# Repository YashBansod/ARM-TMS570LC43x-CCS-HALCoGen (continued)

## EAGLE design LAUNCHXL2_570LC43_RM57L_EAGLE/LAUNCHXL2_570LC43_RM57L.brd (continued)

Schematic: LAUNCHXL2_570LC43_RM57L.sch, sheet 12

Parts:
C58, C59, C60, C61, C63, C68: 0.1uF; C0201; PARTNO CL03A104MQ3NNNC
C62, C70: 0.01uF; C0201; PARTNO CL03A103KQ3NNNC
C65, C67, C71: 1uF; C0402K; PARTNO GRM155R60J105KE19D
J11: MAGJACKARJCO2-111006E; DUAL_ABRACRON_ARJC02_111006K_PULSE_J00-0065NL; PARTNO ARJC02-111006K
R8, R9, R11, R47: 0; R0201; PARTNO RC0201JR-070RL
R20: 4.87K; R0201; PARTNO CRCW02014K87FKED
R23, R24, R36, R37, R38, R46: 49.9; R0201; PARTNO CRCW020149R9FNED
RP11: 2.2K; RP8_1506_1606; PARTNO MNR18E0APJ222
U4: DP83630_RHS_48; SQA48A; PARTNO DP83630SQE/NOPB

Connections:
+3V3: J11.9 (AN1), J11.12 (AN2), R8.1, R9.1, R11.1, RP11.7 (1), RP11.11 (1), RP11.13 (1); also elsewhere on the board
ECLK1T: U4.34 (XIN); also elsewhere on the board
ESHLD: J11.7 (SH1), J11.8 (SH2), R47.1
ETHRD_N: J11.6 (RD-), R37.2, U4.13 (RD-)
ETHRD_P: J11.3 (RD+), R36.2, U4.14 (RD+)
ETHTD_N: J11.2 (TD-), R24.2, U4.16 (TD-)
ETHTD_P: J11.1 (TD+), R23.2, U4.17 (TD+)
GIOA_3/N2HET2_2: RP11.4 (2), U4.7 (PWRDOWN/INTN); also elsewhere on the board
GIOA_4: U4.29 (RESET_N); also elsewhere on the board
GND: C58.2, C59.2, C60.2, C61.2, C62.2, C63.2, C65.2, C67.2, C68.2, C70.2, C71.2, R20.1, R47.2, RP11.1, RP11.3 (1), RP11.9 (1), U4.15 (CD_VSS), U4.18 (ANAVSS), U4.35 (IO_CORE_VSS), U4.47 (IO_VSS), U4.49 (DAP); also elsewhere on the board
MDCLK: U4.31 (MDC); also elsewhere on the board
MDIO: RP11.8 (2), U4.30 (MDIO); also elsewhere on the board
MII_COL: U4.42 (COL); also elsewhere on the board
MII_CRS: RP11.12 (2), U4.40 (CRS/CRS_DV); also elsewhere on the board
MII_RXCLK/MII_RX_AVCLK4: U4.38 (RX_CLK); also elsewhere on the board
MII_RXD_0: U4.46 (RXD_0); also elsewhere on the board
MII_RXD_1: U4.45 (RXD_1); also elsewhere on the board
MII_RXD_2: U4.44 (RXD_2); also elsewhere on the board
MII_RXD_3: U4.43 (RXD_3); also elsewhere on the board
MII_RX_DV: RP11.10 (2), U4.39 (RX_DV); also elsewhere on the board
MII_RX_ER: RP11.14 (2), U4.41 (RX_ER); also elsewhere on the board
MII_TXCLK/MII_TX_AVCLK4: U4.1 (TX_CLK); also elsewhere on the board
MII_TXD_0: U4.3 (TXD_0); also elsewhere on the board
MII_TXD_1: U4.4 (TXD_1); also elsewhere on the board
MII_TXD_2: U4.5 (TXD_2); also elsewhere on the board
MII_TXD_3: U4.6 (TXD_3); also elsewhere on the board
MII_TXEN: U4.2 (TX_EN); also elsewhere on the board
N2HET1_15/MIBSPI1NCS_4/N2HET2_22/ECAP1: U4.27 (LED_SPEED/FX_SD); also elsewhere on the board
N2HET1_21/EMIF_NDQM_2: U4.36 (GPIO8); also elsewhere on the board
N2HET1_25: U4.37 (GPIO9); also elsewhere on the board
N2HET1_31: U4.25 (GPIO4); also elsewhere on the board
N2HET2_4: R38.2, U4.28 (LED_LINK); also elsewhere on the board
N2HET2_5: R46.2, U4.26 (LED_ACT); also elsewhere on the board
N2HET2_6: U4.21 (GPIO1); also elsewhere on the board
N2HET2_22: U4.22 (GPIO2); also elsewhere on the board
N2HET2_23: U4.23 (GPIO3); also elsewhere on the board
unnamed: J11.10 (CAT1), R38.1
unnamed: J11.11 (CAT2), R46.1
PHYAVDD: C63.1, C70.1, C71.1, R9.2, U4.19 (ANA33VDD)
PHYIOVDD: C62.1, C67.1, C68.1, R8.2, U4.32 (IO_VDD), U4.48 (IO_VDD_2)
PHY_VCT: C58.1, C59.1, C60.1, C61.1, C65.1, J11.4 (CT1), J11.5 (CT2), R11.2, R23.1, R24.1, R36.1, R37.1
RBIAS: R20.2, U4.20 (VREF)

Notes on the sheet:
PHY ADDRESS ================ PHYADDR[4:0] = 00001b MCU & PHY Pulls Match PHYAD0 (COL) - PU PHYAD1 (RXD0) - PD PHYAD2 (RXD1) - PD PHYAD3 (RXD2) - PD PHYAD4 (RXD3) - PD
FOR CENTER TAPS
spare

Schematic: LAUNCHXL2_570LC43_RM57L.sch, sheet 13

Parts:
J12, J13: DF40C-60DP-0.4V(51); PARTNO DF40C-60DP-0.4V(51)

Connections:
+3V3: J12.3, J12.4, J12.59, J12.60, J13.3, J13.4, J13.59, J13.60; also elsewhere on the board
EMIF_ADDR_0/N2HET2_1: J13.50; also elsewhere on the board
EMIF_ADDR_1/N2HET2_3: J13.48; also elsewhere on the board
EMIF_ADDR_6/RTP_DATA_13/N2HET2_11: J13.44; also elsewhere on the board
EMIF_ADDR_7/RTP_DATA_12/N2HET2_13: J13.42; also elsewhere on the board
EMIF_ADDR_8/RTP_DATA_11/N2HET2_15: J13.38; also elsewhere on the board
EMIF_ADDR_9/RTP_DATA_10: J13.36; also elsewhere on the board
EMIF_ADDR_10/RTP_DATA_9: J13.32; also elsewhere on the board
EMIF_ADDR_11/RTP_DATA_8: J13.39; also elsewhere on the board
EMIF_ADDR_12/RTP_DATA_6: J13.33; also elsewhere on the board
EMIF_ADDR_13/RTP_DATA_5: J13.29; also elsewhere on the board
EMIF_ADDR_14/RTP_DATA_4: J13.27; also elsewhere on the board
EMIF_ADDR_15/RTP_DATA_3: J13.23; also elsewhere on the board
EMIF_ADDR_16/RTP_DATA_2: J13.21; also elsewhere on the board
EMIF_ADDR_17/RTP_DATA_1: J13.17; also elsewhere on the board
EMIF_ADDR_18/RTP_DATA_0: J13.15; also elsewhere on the board
EMIF_ADDR_19/RTP_NENA: J13.11; also elsewhere on the board
EMIF_ADDR_20/RTP_NSYNC: J13.9; also elsewhere on the board
EMIF_ADDR_21/RTP_CLK: J13.5; also elsewhere on the board
EMIF_BA_1/N2HET2_5: J13.35; also elsewhere on the board
EMIF_NCS_0/RTP_DATA_15/N2HET2_7: J12.5; also elsewhere on the board
EMIF_NCS_2/GIOB_4: J12.9; also elsewhere on the board
EMIF_NCS_3/RTP_DATA_14/N2HET2_9: J12.11; also elsewhere on the board
EMIF_NCS_4/RTP_DATA_7/GIOB_5: J12.15; also elsewhere on the board
EMIF_NWE/EMIF_RNW: J12.51; also elsewhere on the board
ETMDATA_2: J12.29; also elsewhere on the board
ETMDATA_3: J12.33; also elsewhere on the board
ETMDATA_4: J12.35; also elsewhere on the board
ETMDATA_5: J12.39; also elsewhere on the board
ETMDATA_6: J12.41; also elsewhere on the board
ETMDATA_7: J12.45; also elsewhere on the board
ETMDATA_8/EMIF_ADDR_5: J12.47; also elsewhere on the board
ETMDATA_9/EMIF_ADDR_4: J13.6; also elsewhere on the board
ETMDATA_10/EMIF_ADDR_3: J13.8; also elsewhere on the board
ETMDATA_11/EMIF_ADDR_2: J13.12; also elsewhere on the board
ETMDATA_12/EMIF_BA_0: J13.41; also elsewhere on the board
ETMDATA_13/EMIF_NOE: J13.45; also elsewhere on the board
ETMDATA_14/EMIF_NDQM_1: J13.47; also elsewhere on the board
ETMDATA_15/EMIF_NDQM_0: J13.51; also elsewhere on the board
ETMDATA_16/EMIF_DATA_0: J12.27; also elsewhere on the board
ETMDATA_17/EMIF_DATA_1: J12.23; also elsewhere on the board
ETMDATA_18/EMIF_DATA_2: J12.21; also elsewhere on the board
ETMDATA_19/EMIF_DATA_3: J12.17; also elsewhere on the board
ETMDATA_20/EMIF_DATA_4: J13.14; also elsewhere on the board
ETMDATA_21/EMIF_DATA_5: J13.18; also elsewhere on the board
ETMDATA_22/EMIF_DATA_6: J13.20; also elsewhere on the board
ETMDATA_23/EMIF_DATA_7: J13.24; also elsewhere on the board
ETMDATA_24/EMIF_DATA_8/N2HET2_24/MIBSPI5NCS_4: J13.26; also elsewhere on the board
ETMDATA_25/EMIF_DATA_9/N2HET2_25/MIBSPI5NCS_5: J13.30; also elsewhere on the board
EXTERNAL_DEBUG: J12.20; also elsewhere on the board
FDONE: J13.54; also elsewhere on the board
FPROG: J12.42; also elsewhere on the board
FSCLK: J13.55; also elsewhere on the board
FSIMO: J13.53; also elsewhere on the board
FSOMI: J13.56; also elsewhere on the board
FTCK: J12.30; also elsewhere on the board
FTDI: J12.36; also elsewhere on the board
FTDO: J12.32; also elsewhere on the board
FTMS: J12.38; also elsewhere on the board
GND: J12.1, J12.2, J12.7, J12.10, J12.13, J12.16, J12.19, J12.22, J12.25, J12.28, J12.31, J12.34, J12.37, J12.40, J12.43, J12.46, J12.49, J12.52, J12.57, J12.58, J13.1, J13.2, J13.7, J13.10, J13.13, J13.16, J13.19, J13.22, J13.25, J13.28, J13.31, J13.34, J13.37, J13.40, J13.43, J13.46, J13.49, J13.52, J13.57, J13.58; also elsewhere on the board
HERCULES_MR_PB: J12.18; also elsewhere on the board
HERCULES_NRST: J12.55; also elsewhere on the board
HERCULES_NTRST: J12.26; also elsewhere on the board
HERCULES_RTCK: J12.24; also elsewhere on the board
HERCULES_TCK: J12.6; also elsewhere on the board
HERCULES_TDI: J12.14; also elsewhere on the board
HERCULES_TDO: J12.12; also elsewhere on the board
HERCULES_TMS: J12.8; also elsewhere on the board
MIBSPI1CLK: J12.44; also elsewhere on the board
N2HET1_8/MIBSPI1SIMO_1/MII_TXD_3: J12.48; also elsewhere on the board
N2HET1_10/MIBSPI4NCS_4/MII_TXCLK/MII_TX_AVCLK4/NTZ1_3: J12.50; also elsewhere on the board
N2HET1_17/EMIF_NOE/SCI4RX: J12.54; also elsewhere on the board
N2HET1_19/EMIF_NDQM_0/SCI4TX: J12.56; also elsewhere on the board
NERROR: J12.53; also elsewhere on the board

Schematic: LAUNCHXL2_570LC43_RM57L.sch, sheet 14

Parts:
J14, J15: DF40C-60DP-0.4V(51); PARTNO DF40C-60DP-0.4V(51)

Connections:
+3V3: J14.3, J14.4, J14.59, J14.60, J15.3, J15.4, J15.59, J15.60; also elsewhere on the board
AD1EVT/MII_RX_ER/RMII_RX_ER/NTZ1_1: J14.12; also elsewhere on the board
AD2IN_16: J14.47; also elsewhere on the board
AD2IN_17: J14.51; also elsewhere on the board
AD2IN_18: J14.53; also elsewhere on the board
AD2IN_19: J14.55; also elsewhere on the board
AD2IN_20: J14.56; also elsewhere on the board
AD2IN_21: J14.54; also elsewhere on the board
AD2IN_22: J14.50; also elsewhere on the board
AD2IN_23: J14.48; also elsewhere on the board
DMM_CLK: J14.5; also elsewhere on the board
DMM_DATA_0: J14.15; also elsewhere on the board
DMM_DATA_1: J14.16; also elsewhere on the board
DMM_NENA: J14.9; also elsewhere on the board
DMM_SYNC: J14.11; also elsewhere on the board
EMIF_CKE: J15.48; also elsewhere on the board
EMIF_CLK/ECLK2: J15.50; also elsewhere on the board
EMIF_NCAS/GIOB_3: J15.38; also elsewhere on the board
EMIF_NRAS/GIOB_6: J15.42; also elsewhere on the board
EMIF_NWAIT/GIOB_7: J15.44; also elsewhere on the board
EPWM1A: J15.9; also elsewhere on the board
EPWM1B: J15.5; also elsewhere on the board
ETMDATA_0: J15.6; also elsewhere on the board
ETMDATA_1: J15.8; also elsewhere on the board
ETMDATA_26/EMIF_DATA_10/N2HET2_26: J15.36; also elsewhere on the board
ETMDATA_27/EMIF_DATA_11/N2HET2_27: J15.32; also elsewhere on the board
ETMDATA_28/EMIF_DATA_12/N2HET2_28/GIOA_0: J15.30; also elsewhere on the board
ETMDATA_29/EMIF_DATA_13/N2HET2_29/GIOA_1: J15.26; also elsewhere on the board
ETMDATA_30/EMIF_DATA_14/N2HET2_30/GIOA_3: J15.24; also elsewhere on the board
ETMDATA_31/EMIF_DATA_15/N2HET2_31/GIOA_4: J15.20; also elsewhere on the board
ETMTRACECLKIN/EXTCLKIN2/GIOA_5: J15.18; also elsewhere on the board
ETMTRACECLKOUT/GIOA_6: J15.12; also elsewhere on the board
ETMTRACECTL/GIOA_7: J15.14; also elsewhere on the board
FINT: J15.54; also elsewhere on the board
FM0: J14.42; also elsewhere on the board
FM1: J14.44; also elsewhere on the board
FM2: J14.45; also elsewhere on the board
GIOB_2/DCAN4TX: J14.8; also elsewhere on the board
GIOB_3/DCAN4RX: J14.6; also elsewhere on the board
GND: J14.1, J14.2, J14.7, J14.10, J14.13, J14.19, J14.22, J14.25, J14.28, J14.31, J14.34, J14.37, J14.40, J14.43, J14.46, J14.49, J14.52, J14.57, J14.58, J15.1, J15.2, J15.7, J15.10, J15.13, J15.16, J15.19, J15.22, J15.25, J15.28, J15.31, J15.34, J15.37, J15.40, J15.43, J15.46, J15.49, J15.52, J15.57, J15.58; also elsewhere on the board
MIBSPI1CLK: J15.56; also elsewhere on the board
MIBSPI1NCS_0/MIBSPI1SOMI_1/MII_TXD_2/ECAP6: J15.39; also elsewhere on the board
MIBSPI1NCS_1/MII_COL/N2HET1_17/EQEP1S: J15.41; also elsewhere on the board
MIBSPI1NCS_2/MDIO/N2HET1_19: J15.45; also elsewhere on the board
MIBSPI1NENA/MII_RXD_2/N2HET1_23/ECAP4: J15.51; also elsewhere on the board
MIBSPI1SIMO_0: J15.53; also elsewhere on the board
MIBSPI1SOMI_0: J15.55; also elsewhere on the board
MIBSPI3NCS_0/AD2EVT/EQEP1I: J14.14; also elsewhere on the board
MIBSPI3NCS_1/MDCLK/N2HET1_25: J15.15; also elsewhere on the board
MIBSPI3NCS_2/I2C1_SDA/N2HET1_27/NTZ1_2: J15.17; also elsewhere on the board
MIBSPI3NCS_3/I2C1_SCL/N2HET1_29/NTZ1_1: J15.21; also elsewhere on the board
MIBSPI5CLK/DMM_DATA_4/MII_TXEN/RMII_TXEN: J14.21; also elsewhere on the board
MIBSPI5NCS_0/DMM_DATA_5/EPWM4A: J14.20; also elsewhere on the board
MIBSPI5NCS_1/DMM_DATA_6: J14.23; also elsewhere on the board
MIBSPI5NCS_2/DMM_DATA_2: J14.17; also elsewhere on the board
MIBSPI5NCS_3/DMM_DATA_3: J14.18; also elsewhere on the board
MIBSPI5NENA/DMM_DATA_7/MII_RXD_3/ECAP5: J14.24; also elsewhere on the board
MIBSPI5SIMO_0/DMM_DATA_8/MII_TXD_1/RMII_TXD_1: J14.27; also elsewhere on the board
MIBSPI5SIMO_1/DMM_DATA_9/AD1EXT_SEL_0: J14.26; also elsewhere on the board
MIBSPI5SIMO_2/DMM_DATA_10/AD1EXT_SEL_1: J14.29; also elsewhere on the board
MIBSPI5SIMO_3/DMM_DATA_11/I2C2_SDA/AD1EXT_SEL_2: J14.30; also elsewhere on the board
MIBSPI5SOMI_0/DMM_DATA_12/MII_TXD_0/RMII_TXD_0: J14.33; also elsewhere on the board
MIBSPI5SOMI_1/DMM_DATA_13/AD1EXT_SEL_3: J14.32; also elsewhere on the board
MIBSPI5SOMI_2/DMM_DATA_14/AD1EXT_SEL_4: J14.35; also elsewhere on the board
MIBSPI5SOMI_3/DMM_DATA_15/I2C2_SCL/AD1EXT_ENA: J14.36; also elsewhere on the board
N2HET1_1/MIBSPI4NENA/N2HET2_8/EQEP2A: J15.33; also elsewhere on the board
N2HET1_3/MIBSPI4NCS_0/N2HET2_10/EQEP2B: J15.35; also elsewhere on the board
N2HET1_12/MIBSPI4NCS_5/MII_CRS/RMII_CRS_DV: J15.23; also elsewhere on the board
N2HET1_20/EMIF_NDQM_1/EPWM6B: J15.11; also elsewhere on the board
N2HET1_24/MIBSPI1NCS_5/MII_RXD_0/RMII_RXD_0: J15.47; also elsewhere on the board
N2HET1_26/MII_RXD_1/RMII_RXD_1: J15.29; also elsewhere on the board
N2HET1_28/MII_RXCLK/RMII_REFCLK/MII_RX_AVCLK4: J14.38; also elsewhere on the board
N2HET1_30/MII_RX_DV/EQEP2S: J15.27; also elsewhere on the board
N2HET2_19/LIN2RX: J14.39; also elsewhere on the board
N2HET2_20/LIN2TX: J14.41; also elsewhere on the board

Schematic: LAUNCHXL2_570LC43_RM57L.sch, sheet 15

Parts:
LED7, LED8: GRN; CHIPLED_0603; PARTNO QBLP601-AG
R7: 49.9; R0201; PARTNO CRCW020149R9FNED
R30, R31: 330K; R0201; PARTNO RC0603F334CS
R34, R35: 220K; R0201; PARTNO RC0603F224CS
RP12: 2.2K; RP8_1506_1606; PARTNO MNR18E0APJ222
U7: TM4C129ENCPDT; PDT128; PARTNO TM4C129ENCPDTI3

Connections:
+1V2: U7.127 (PD6\AIN5\SSI2XDAT3\T4CCP0\U2RTS\USB0EPEN); also elsewhere on the board
+3V3: R35.2; also elsewhere on the board
+5V_USB: R34.2, U7.96 (PB1\CAN1TX\I2C5SDA\T4CCP1\U1TX\USB0VBUS); also elsewhere on the board
EXTERNAL_DEBUG: U7.41 (PA7\EPI0S9\I2C6SDA\SSI0XDAT3\T3CCP1\U2T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); also elsewhere on the board
FDONE: U7.71 (PM7\T5CCP1\TMPR0\U0RI); also elsewhere on the board
FINT: U7.6 (PQ1\EPI0S21\SSI3FSS); also elsewhere on the board
FM0: U7.74 (PM4\T4CCP0\TMPR3\U0CTS); also elsewhere on the board
FM1: U7.73 (PM5\T4CCP1\TMPR2\U0DCD); also elsewhere on the board
FM2: U7.72 (PM6\T5CCP0\TMPR1\U0DSR); also elsewhere on the board
FPROG: U7.102 (PQ4\DIVSCLK\U1RX); also elsewhere on the board
FSCLK: U7.5 (PQ0\EPI0S20\SSI3CLK); also elsewhere on the board
FSIMO: U7.11 (PQ2\EPI0S22\SSI3XDAT0); also elsewhere on the board
FSOMI: U7.27 (PQ3\EPI0S23\SSI3XDAT1); also elsewhere on the board
FTCK: U7.112 (PN5\EPI0S35\I2C2SCL\U1RI\U3CTS); also elsewhere on the board
FTDI: U7.110 (PN3\EPI0S30\U1DSR\U2CTS); also elsewhere on the board
FTDO: U7.111 (PN4\EPI0S34\I2C2SDA\U1DTR\U3RTS); also elsewhere on the board
FTMS: U7.109 (PN2\EPI0S29\U1DCD\U2RTS); also elsewhere on the board
GND: LED7.C, LED8.C, R30.1, R31.1, U7.61 (PK6\EN0LED1\EPI0S25\I2C4SCL\M0FAULT1), U7.62 (PK5\EN0LED2\EPI0S31\I2C3SDA\M0PWM7); also elsewhere on the board
HERCULES_ICORE: U7.15 (PE0\AIN3\U1RTS); also elsewhere on the board
HERCULES_MR_PB: U7.40 (PA6\EPI0S8\I2C6SCL\SSI0XDAT2\T3CCP0\U2R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); also elsewhere on the board
HERCULES_NRST: U7.25 (PC4\C1-\EPI0S7\U7RX); also elsewhere on the board
HERCULES_NTRST: U7.107 (PN0\U1RTS); also elsewhere on the board
HERCULES_RTCK: U7.108 (PN1\U1CTS); also elsewhere on the board
HERCULES_TCK: R7.2; also elsewhere on the board
HERCULES_TDI: U7.38 (PA5\I2C7SDA\SSI0XDAT1\T2CCP1\U3TX); also elsewhere on the board
HERCULES_TDO: U7.37 (PA4\I2C7SCL\SSI0XDAT0\T2CCP0\U3RX); also elsewhere on the board
HERCULES_TMS: U7.36 (PA3\I2C8SDA\SSI0FSS\T1CCP1\U4TX); also elsewhere on the board
ITCK: U7.100 (PC0\SWCLK\TCK); also elsewhere on the board
ITDI: U7.98 (PC2\TDI); also elsewhere on the board
ITDO: U7.97 (PC3\SWO\TDO); also elsewhere on the board
ITMS: U7.99 (PC1\SWDIO\TMS); also elsewhere on the board
LIN1RX: U7.34 (PA1\CAN0TX\I2C9SDA\T0CCP1\U0TX); also elsewhere on the board
LIN1TX: U7.33 (PA0\CAN0RX\I2C9SCL\T0CCP0\U0RX); also elsewhere on the board
unnamed: RP12.3 (1), U7.4 (PD3\AIN12\I2C8SDA\SSI2CLK\T1CCP1)
unnamed: LED7.A, RP12.4 (2)
unnamed: RP12.1, U7.3 (PD2\AIN13\C2O\I2C8SCL\SSI2FSS\T1CCP0)
unnamed: R7.1, U7.35 (PA2\I2C8SCL\SSI0CLK\T1CCP0\U4RX)
unnamed: R31.2, R35.1, U7.126 (PD5\AIN6\SSI1XDAT3\T3CCP1\U2TX)
unnamed: R30.2, R34.1, U7.1 (PD0\AIN15\C0O\I2C7SCL\SSI2XDAT1\T0CCP0)
unnamed: LED8.A, RP12.2
USBD_N: U7.93 (PL7\T1CCP1\USB0DM); also elsewhere on the board
USBD_P: U7.94 (PL6\T1CCP0\USB0DP); also elsewhere on the board
USB_HIPWR_ENA: U7.118 (PP0\C2+\SSI3XDAT2\U6RX); also elsewhere on the board
USB_ID: U7.95 (PB0\CAN1RX\I2C5SCL\T4CCP0\U1RX\USB0ID); also elsewhere on the board
VERSION_0: U7.63 (PK4\EN0LED0\EPI0S32\I2C3SCL\M0PWM6)
VERSION_3: U7.60 (PK7\EPI0S24\I2C4SDA\M0FAULT2\RTCCLK\U0RI)

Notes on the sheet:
VERSION_1
VERSION_2
VERSION = 1001b
XDS110 DEBUG PROBE

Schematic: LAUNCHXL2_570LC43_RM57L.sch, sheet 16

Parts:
C34, C39: 33pF; C0201; PARTNO CC0201JRNPO8BN330
C35, C40, C42, C49: 0.01uF; C0201; PARTNO CL03A103KQ3NNNC
C36, C37, C41, C44: 1000pF; C0201; PARTNO CC0201KRX7R8BB102
C38, C43, C45, C47, C48: 0.1uF; C0201; PARTNO CL03A104MQ3NNNC
C46, C50: 10uF; C0805K; PARTNO C0805C106K8PACTU
J19: FTSH-105-01-F-DV_SMD; FTSH-105-01-F-DV; PARTNO PJ-002BH-SMT-TR
R5: 4.87K; R0201; PARTNO CRCW02014K87FKED
R40: 49.9; R0201; PARTNO CRCW020149R9FNED
RP12: 2.2K; RP8_1506_1606; PARTNO MNR18E0APJ222
U7: TM4C129ENCPDT; PDT128; PARTNO TM4C129ENCPDTI3
U8: LM4040D30_DBZ_3; DBZ3; PARTNO LM4040D20IDBZR
Y2: 16.00MHZ; CSM-3X; PARTNO ECS-160-20-3X-TR

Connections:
+1V2_TM4C: C47.1, C49.1, C50.1, U7.87 (VDDC), U7.115 (VDDC)
+3V3: C35.1, C36.1, C37.1, C38.1, C40.1, C41.1, C42.1, C43.1, C44.1, C45.1, C46.1, J19.1, R40.1, RP12.5 (1), U7.7 (VDD), U7.8 (VDDA), U7.16 (VDD), U7.26 (VDD), U7.28 (VDD), U7.39 (VDD), U7.47 (VDD), U7.51 (VDD), U7.52 (VDD), U7.68 (VBAT), U7.69 (VDD), U7.79 (VDD), U7.90 (VDD), U7.101 (VDD), U7.113 (VDD), U7.122 (VDD); also elsewhere on the board
GND: C34.2, C35.2, C36.2, C37.2, C38.2, C39.2, C40.2, C41.2, C42.2, C43.2, C44.2, C45.2, C46.2, C47.2, C48.2, C49.2, C50.2, J19.3, J19.5, J19.7, J19.9, R5.1, U7.10 (GNDA), U7.17 (GND), U7.48 (GND), U7.55 (GND), U7.58 (GND), U7.64 (!WAKE), U7.66 (XOSC0), U7.80 (GND), U7.114 (GND), U8.2 (ANODE); also elsewhere on the board
IRSTN: J19.10, RP12.6 (2), U7.70 (!RST)
ITCK: J19.4; also elsewhere on the board
ITDI: J19.8; also elsewhere on the board
ITDO: J19.6; also elsewhere on the board
ITMS: J19.2; also elsewhere on the board
unnamed: R5.2, U7.59 (RBIAS)
OSC0: C34.1, U7.88 (OSC0), Y2.2
OSC1: C39.1, U7.89 (OSC1), Y2.1
VREFA+: C48.1, R40.2, U7.9 (VREFA+), U8.1 (CATHODE)

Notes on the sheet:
3.0V ADC REFERENCE
J19 not intended for normal use. Locate on Back Side / Cover in SM.
XDS110 DEBUG PROBE

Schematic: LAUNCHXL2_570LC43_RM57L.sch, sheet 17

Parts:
C51: 4.7uF; C0603K; PARTNO CC0603KRX5R5BB475
C52: 0.1uF; C0201; PARTNO CL03A104MQ3NNNC
C53, C54: 4700pF; C0201; PARTNO GRM033R71A472KA01D
C55: 100uF; C1206K; PARTNO GRM31CR60J107ME39L
FB1, FB2: 30 OHM @ 100MHz; R0603; PARTNO CIS10P300AC
FID1, FID2, FID3, FID4, FID5: DNP; FIDUCIAL_1MM; PARTNO BOM_EXCLUDE
J16: USB_MICRO_B_SMD; PARTNO 10118192-0001LF
J17: JACK-PLUGCUI_PJ002BH; CUI_PJ002BH; PARTNO FTSH-105-01-F-DV
JP6: SHORT; JP1_SHORT; PARTNO GEC02DABN-M30
LED9: RED; CHIPLED_0603; PARTNO LS Q976-NR-1
MH1, MH2, MH3, MH4: DNP; MH_94_200; PARTNO BOM_EXCLUDE
PAD9, PAD10, PAD11, PAD12: DNP; 2,54/1,1; PARTNO BOM_EXCLUDE
PTC1: 3A IH / 5A IT; R1812; PARTNO 0ZCG0300FF2B
R43: 220K; R0201; PARTNO RC0603F224CS
R44: 1M; R0201; PARTNO RC0201JR-071ML
R45: 61.9K; R0201; PARTNO CRCW020161K9FKED
RP12: 2.2K; RP8_1506_1606; PARTNO MNR18E0APJ222
U3: TPD4E004_DRY_6; DRY6; PARTNO TPD4E004DRYR
U9: TPS2553_DBV_6; DBV6; PARTNO TPS2553DBVR

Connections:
5V_USB_LIMITED: JP6.1, U9.6 (OUT)
+5V: C55.1, JP6.2, PTC1.1; also elsewhere on the board
+5V_JACK: J17.1A (3), J17.1B (3), PTC1.2
+5V_USB: C51.1, FB1.2 (B), RP12.11 (1), RP12.14 (2), U3.5 (IO4), U9.1 (IN); also elsewhere on the board
GND: C51.2, C52.2, C54.2, C55.2, FB2.2 (B), J17.2 (1), J17.3 (2), PAD9.1, PAD10.1, PAD11.1, PAD12.1, R43.2, U9.2 (GND); also elsewhere on the board
ILIM: C54.1, R43.1, R45.2, U9.5 (ILIM)
unnamed: LED9.A, RP12.12 (2)
unnamed: C52.1, RP12.13 (1), U9.3 (EN)
USBD_N: J16.2 (D-), U3.1 (IO1); also elsewhere on the board
USBD_P: J16.3 (D+), U3.2 (IO2); also elsewhere on the board
USBVDD: FB1.1 (A), J16.1 (USBVDD), U3.6 (VCC)
USBVSS: C53.1, FB2.1 (A), J16.5 (USBVSS), R44.2, U3.3 (GND)
USB_HIPWR_ENA: R45.1; also elsewhere on the board
USB_ID: J16.4 (ID), U3.4 (IO3); also elsewhere on the board
USB_PWRFAULT: LED9.C, U9.4 (*FAULT)
USB_SHIELD: C53.2, J16.S1, J16.S2, J16.S3, J16.S4, J16.S5, J16.S6, R44.1

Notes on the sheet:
CURRENT LIMITING FOR BUS POWERED OPERATION
DEBUG USB XDS110
REMOVE JUMPER TO POWER THROUGH BARREL JACK
FIDUCIALS
GND POINTS
BOARD
QFP
MNT HOLES

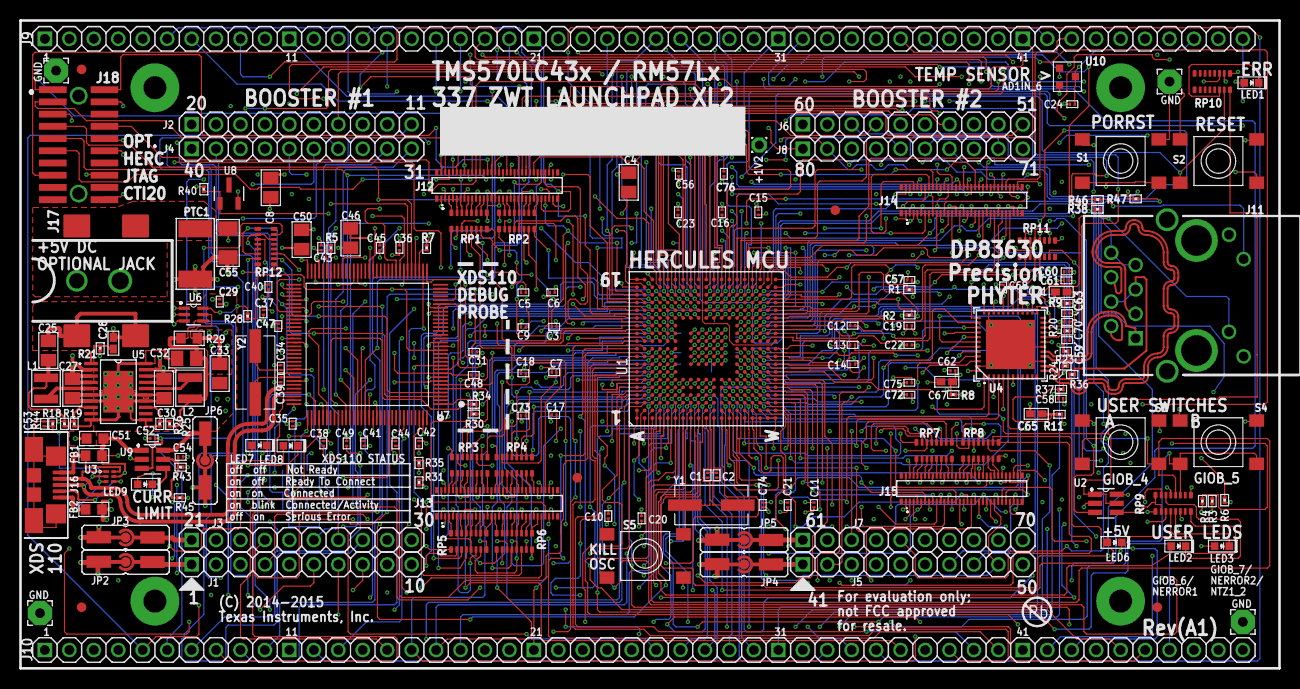
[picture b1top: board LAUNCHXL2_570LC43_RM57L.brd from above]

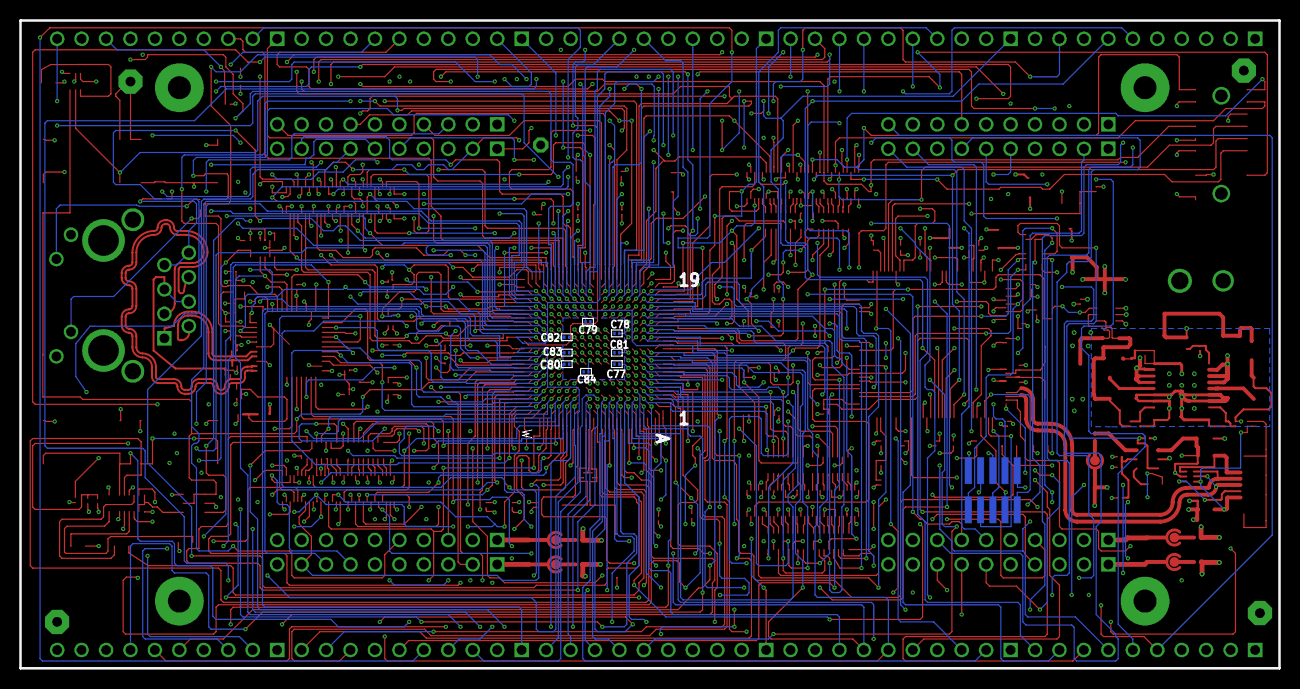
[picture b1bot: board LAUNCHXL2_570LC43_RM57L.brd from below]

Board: 6 copper layers, 130.8 x 67.3 mm, 193 parts (9 on the bottom side), 407 nets.

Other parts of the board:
DRILEGEND: DRILEGEND

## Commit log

2016-12-11 This CCS Project demonstates the toggling of user LEDs on Hercules TMS570LC43x Development board. The GIOB 6 & 7 are toggled with a 1 second delay created by wasting machine cycles.
    This code can be edited to operate on any GIO on the board.
2016-12-11 The following project demonstrates the toggling of user LEDs on the Hercules TMS570LC43x Development board using CCS. The LEDs are toggled with a delay of 1000 milli-second using the RTI (Real Time I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
    The following code can be edited to generate a code for
    timer interrupt operations.
2016-12-11 Added Comments to explain the code.
2016-12-11 Corrected a comment in the code.
2016-12-11 The following code toggles the hetPORT1 pin 1 & 2 with a duration of 1 second by wasting machine cycles. The code is written on CCS 6 and Driver Libraries were created using the TI's HALCoGen.
    This code can be edited to operate on the hetPORT 1 & 2.
2016-12-11 The following code demonstrates the toggling of hetPORT1 pin 1 & 2 with a duration of 100 milli-seconds using the RTI (Real Time Interrupts). The code is written using CCS and HALCoGen.
    This code can be edited to operate the hetPORT 1 & 2 with real time
    interrupts.
2016-12-13 This code sends an array of predefined ASCII Characters to the SCI configured as UART port to an UART enabled device. The Code is written using CCS and HALCoGen.
    This code can be used to publish data through UART contineously from
    the microcontroller.
2016-12-13 This program recieves ASCII characters from a UART enabled device and stores it in a variable. The variable is also echoed back to the user. Also initially a prompt is transmitted to the user for ent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
    This can be modified to recieve data from sensors sending value through
    UART, or control microcontroller through UART
2016-12-15 This project glows the userLEDs when the userBUTTONs are pressed. The project was made using CCS and HALCoGen.
    The code can be edited to have any digital output controlled by a digital
    input.
2016-12-15 Variable names changed. Minor modifications done.
2016-12-15 Variable names changed. Minor modifications made.
2016-12-15 Minor code changes. (rearranged)
2016-12-15 The following project configures the hetPORT1 to generate a PWM of 4.25% duty cycle on PWM0, HET1_8 pin. The code is made using CCS and HALCoGen.
    The following code can be made to give a fixed PWM signal
    to hetPORT 1 and 2 pins.
2016-12-15 The following project generates a varying PWM on HET1_8 pin. The Period is 20ms and inital duty cycle 4.00%(800us). The duty cycle can be changed in steps of 0.01 by pressing the userSWITCH A & B. Th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
    The code can be edited to obtain varying duty cycles on
    HET PORT 1 & 2.
2017-01-21 The project sends the ADC1[6] value through the UART1. The project was made using CCS and HALCoGen. The code can be edited to transmit any ADC reading or Digital reading through a UART connection.
2017-01-21 Transmit data of multiple ADC channels through UART. The project was made in CCS and HALCoGen. The code can be used to read data through any ADC pin and transmit its reading through a UART channel al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
2017-01-21 This project controls the ETPWM duty with an ADC input. This project was made using CCS and HALCoGen. The project can be edited to get a varying duty PWM from the ETPWM module. The input to vary the 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
2017-01-28 This is the board schematics and the pcb layout The document can be viewed on Cadsoft Eagle. Refer the document for pin layout, board layout etc.
2017-01-28 The project publishes data on CAN1, MessageBox1. The project was made using CCS and HALCoGen. For connecting to the CAN bus the SN65HVD231QD tranceiver was used. The code can be modified to transmit 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
2017-01-28 The project receives data on CAN1 and transmits on UART. The project was made using CCS and HALCoGen. For connecting to the CAN bus the SN65HVD231QD tranceiver was used. The code can be modified to r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
2017-01-28 Temporary Deletion
2017-01-28 This Project demonstates the toggling of user LEDs on Hercules TMS570LC43x Development board. The GIOB 6 & 7 are toggled with a 1 second delay created by wasting machine cycles.
    The Project was made using CCS and HALCoGen.
    This code can be edited to operate on any GIO on the board.
2017-01-28 The project toggles the hetPORT1 pin 1 & 2 with a duration of 1 second by wasting machine cycles. The code is written on CCS 6 and Driver Libraries were created using the TI's HALCoGen.
    This code can be edited to operate on the hetPORT 1 & 2.
2017-01-28 This project sends ASCII Characters through SCI configured as UART port to an UART enabled device. The Code is written using CCS and HALCoGen.
    This code can be used to publish data through UART contineously from
    the microcontroller.
2017-03-22 The Project establishes a Multi-Node Can Network interface. There are three sub-projects for three different nodes, These can be programmed/copied to add different nodes. The address and message of t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
2017-03-22 The project implements a multi-channel CAN network with internal loopback. The message transmitted on a channel by a node is internally looped back and is received by the same node. The project was m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
